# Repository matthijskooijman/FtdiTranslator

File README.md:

FtdiTranslator PCB design
=========================

This repository contains the PCB design for an serial level translator
board. It is intended to be used with a 6-pin USB-to-serial adapter that
used the "FTDI" pinout, which is commonly used for Arduino boards as
well (e.g. by the Pro Mini).

When using such an adapter, the voltage levels must typically be matched
with the target board. This is fairly easy for standard 5V and 3.3V
boards (by having two adapters, or having an adapter that can switch
between both voltages), but when the target runs on a non-standard
voltage (e.g. powered by batteries), you need to insert a converter
board in between.

This board provides such conversion on the TX, RX and DTR lines.

The translator circuit is pretty much copied from [this Adafruit
board][AdafruitBoard] (except with a different transistor). Also see
[AN10441 from NXP][AN10441] that explains how the translator works.

[AdafruitBoard]: https://www.adafruit.com/product/757
[AN10441]: https://www.nxp.com/docs/en/application-note/AN10441.pdf

The repository contains the KiCad design files for the board, under
"Releases" in github I also have pre-generated gerber files to use. I
have a few spare boards from my own order, which you can [order through
tindie][tindie].

[tindie]: https://www.tindie.com/products/12036/

Features
--------
 - Bidirectional, so works high-to-low as well as low-to-high voltage.
 - Room for a regulator, so the low side can be powered from the high
   side. The regulator output voltage is fixed, but different versions
   are available (2.5V, 2.8V, 3.0V and 3.3V should all work).
 - Regulator can be enabled or disabled using a jumper.
 - When the regulator is not used, both sides should be separately
   powered, but their voltages can be anything (as long as the high side
   has a higher voltage than the low side).
 - Connects the DTR pin, which is typically used for auto-reset during
   the upload process for Arduino boards, so uploading sketches through
   the converter works.
 - The DTR pin can be disconnected using jumpers (jumpers at both sides
   to completely disconnect the pullup resistors too).

Limitations
-----------
 - The low voltage side must use an equal or lower voltage than the high
   voltage side.
 - The low voltage should not be lower than the transistor threshold
   values. The exact value depends on the exact transistor, temperature,
   current, etc. but the [fairchild datasheet for the 2N7000][2N7000]
   notes a typical Vth of 2.1V.

[2N7000]: http://www.mouser.com/ds/2/149/2N7002-8405.pdf

Needed components
-----------------
The components to completely build this design, are:
 - 6x 10k resistors (SMD 0805 package, though 1206 might also fit)
 - 3x 2N7000 transistors (Through-hole TO-92 package)
 - 1x MCP1700 regulator (SMD SOT89-3 package, exact type depends on desired voltage)
 - 2x 1uF capacitor (SMD 0805 package, though 1206 might also fit)
 - 2x 6-pin angled pin header
 - 3x 2-pin straight pin header
 - 3x jumper

Depending on your needs, some parts can be left out:
 - If you do not need to connect DTR, you can leave out one transistor,
   two resistors, two straight pin headers and two jumpers.
 - If you do not need a regulator, you can leave it off as well as the
   two capacitors.
 - If you always need DTR connected or the regulator enabled, you can
   solder in a wire instead of a pin header and a jumper.

License
-------
This design is copyrighted by Matthijs Kooijman and distributed under
the CERN Open Hardware License, version 1.2 or above. See LICENSE.txt
for the full text of the license.

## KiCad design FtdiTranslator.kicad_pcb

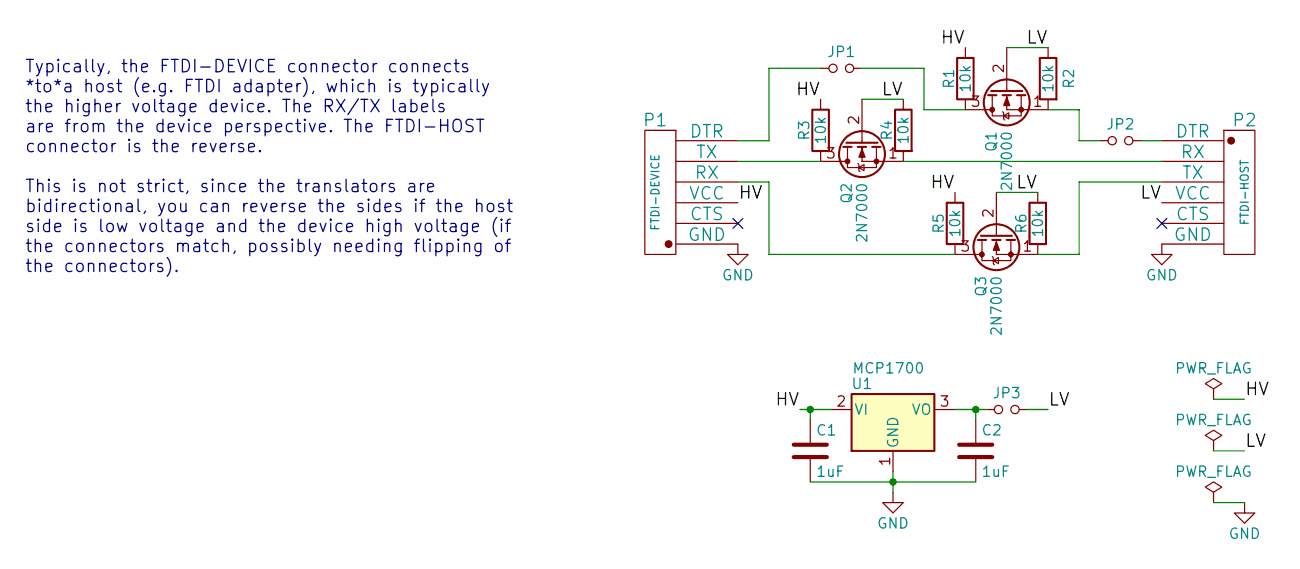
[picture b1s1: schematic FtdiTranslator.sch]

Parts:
C1, C2: 1uF; C_0805_HandSoldering
JP1, JP2, JP3: Jumper_NO_Small; Pin_Header_Straight_1x02_Pitch2.54mm
P1: FTDI-DEVICE; Pin_Header_Angled_1x06_Pitch2.54mm
P2: FTDI-HOST; Pin_Header_Angled_1x06_Pitch2.54mm
Q1, Q2, Q3: 2N7000; TO-92_Inline_Narrow_Oval
R1, R2, R3, R4, R5, R6: 10k; R_0805_HandSoldering
U1: MCP1700; SOT89-3_Housing_Handsoldering

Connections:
/HV: C1.1, P1.3 (VCC), R1.1, R3.1, R5.1, U1.2 (VI)
/LV: JP3.1, P2.4 (VCC), Q1.2 (G), Q2.2 (G), Q3.2 (G), R2.1, R4.1, R6.1
GND: C1.2, C2.2, P1.1 (GND), P2.6 (GND), U1.1 (GND)
unnamed: C2.1, JP3.2, U1.3 (VO)
unnamed: JP1.1, Q1.3 (D), R1.2
unnamed: JP1.2, P1.6 (DTR)
unnamed: JP2.1, P2.1 (DTR)
unnamed: JP2.2, Q1.1 (S), R2.2
unnamed: P1.4 (RX), Q3.3 (D), R5.2
unnamed: P1.5 (TX), Q2.3 (D), R3.2
unnamed: P2.2 (RX), Q2.1 (S), R4.2
unnamed: P2.3 (TX), Q3.1 (S), R6.2

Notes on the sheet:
Typically, the FTDI-DEVICE connector connects *to*a host (e.g. FTDI adapter), which is typically the higher voltage device. The RX/TX labels are from the device perspective. The FTDI-HOST connector is the reverse. This is not strict, since the translators are bidirectional, you can reverse the side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

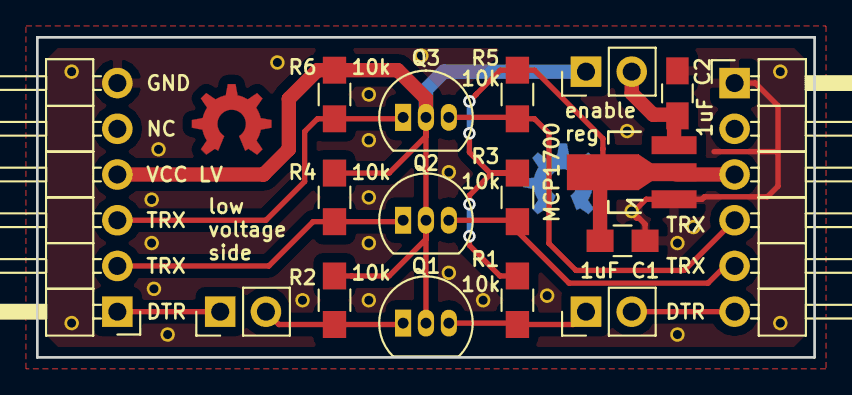
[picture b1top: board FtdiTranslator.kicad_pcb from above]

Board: 2 copper layers, 43.2 x 17.8 mm, 17 parts (0 on the bottom side), 12 nets.

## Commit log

2017-07-07 Add initial version
2017-07-07 Show board dimensions
2017-07-07 Set plot options for Seeed
2017-07-17 Improve silkscreen readability
    This moves some silkscreen text and vias around, and removes some vias
    to improve the silkscreen readability.
2018-04-26 Update to Kicad 5
2018-04-29 Add README
2018-05-17 README: Add link to tindie
2018-05-17 README: Add forgotten link to AN10441
2018-05-17 README: Convert links to reference notation
2018-05-17 README: Add image of the assembled board
2018-05-17 LICENSE: Add file
2018-05-17 README: Remove TODO
    Turns out the version number was already on the silkscreen.
2018-08-15 README: Remove improvements
    Rather use github issues for this.
